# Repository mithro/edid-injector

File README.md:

A device for overriding / injecting EDID information into VGA/DVI/HDMI video
cables.

Based on the idea at
[vgaedidinjector](https://github.com/datenwolf/vgaedidinjector) but with a much
cheaper BOM. It shares no code or design elements with the original design
however.

Uses a Silicon Labs C8051F38x processor as;
 * Has two hardware I2C interfaces (input + output).
 * Has hardware USB subsystem.
 * Runs of 5V power with no external components.
 * Has internal oscillator.
 * I/O pins are 5V compatible.
 * Has good sdcc support.
 * Costs $1.83 USD in individual quantities.
 * Is hand solderable.

More info:
 * [Datasheet](http://www.silabs.com/Support%20Documents/TechnicalDocs/C8051F38x.pdf)
 * SiLab's part number: C8051F387-GQ
 * Digikey part Number: [336-2032-ND](http://www.digikey.com/product-detail/en/C8051F387-GQ/336-2032-ND/2601833)

# Other parts

## Connectors

 * HDMI connectors
  * **With** locking screw flange
   * `CONN RCPT HDMI W/FLANGE R/A SMD`
   * Manufacture part number: [FCI 10029449-002TLF]
   * Digikey part number: [609-1011-ND](http://www.digikey.com/product-search/en?KeyWords=609-1011-ND&WT.z_header=search_go)
   * [Datasheet](http://portal.fciconnect.com/Comergent//fci/drawing/10029449.pdf)
   * 
   * Cost: $1.17 USD in individual quantities.

  * **Without** locking screw flange.
   * `CONN HDMI RECPT 19POS SMT R/A`
   * Manufacture part number: [FCI 10029449-111RLF]
   * Digikey part number: [609-4614-1-ND](http://www.digikey.com/product-detail/en/10029449-111RLF/609-4614-1-ND/2785376)
   * [Datasheet](http://portal.fciconnect.com/Comergent//fci/drawing/10029449.pdf)
   * 
   * Cost: $0.73 USD in individual quantities.

# Editing

The designs in this repository was made using
[KiCad](http://www.kicad-pcb.org/) version **4.0.4**.

# License

Copyright 2014 Tim "mithro" Ansell licensed under a
Creative Commons Attribution-ShareAlike 4.0 International License.

You should have received a copy of the license along with this
work.  If not, see <http://creativecommons.org/licenses/by-sa/4.0/>.

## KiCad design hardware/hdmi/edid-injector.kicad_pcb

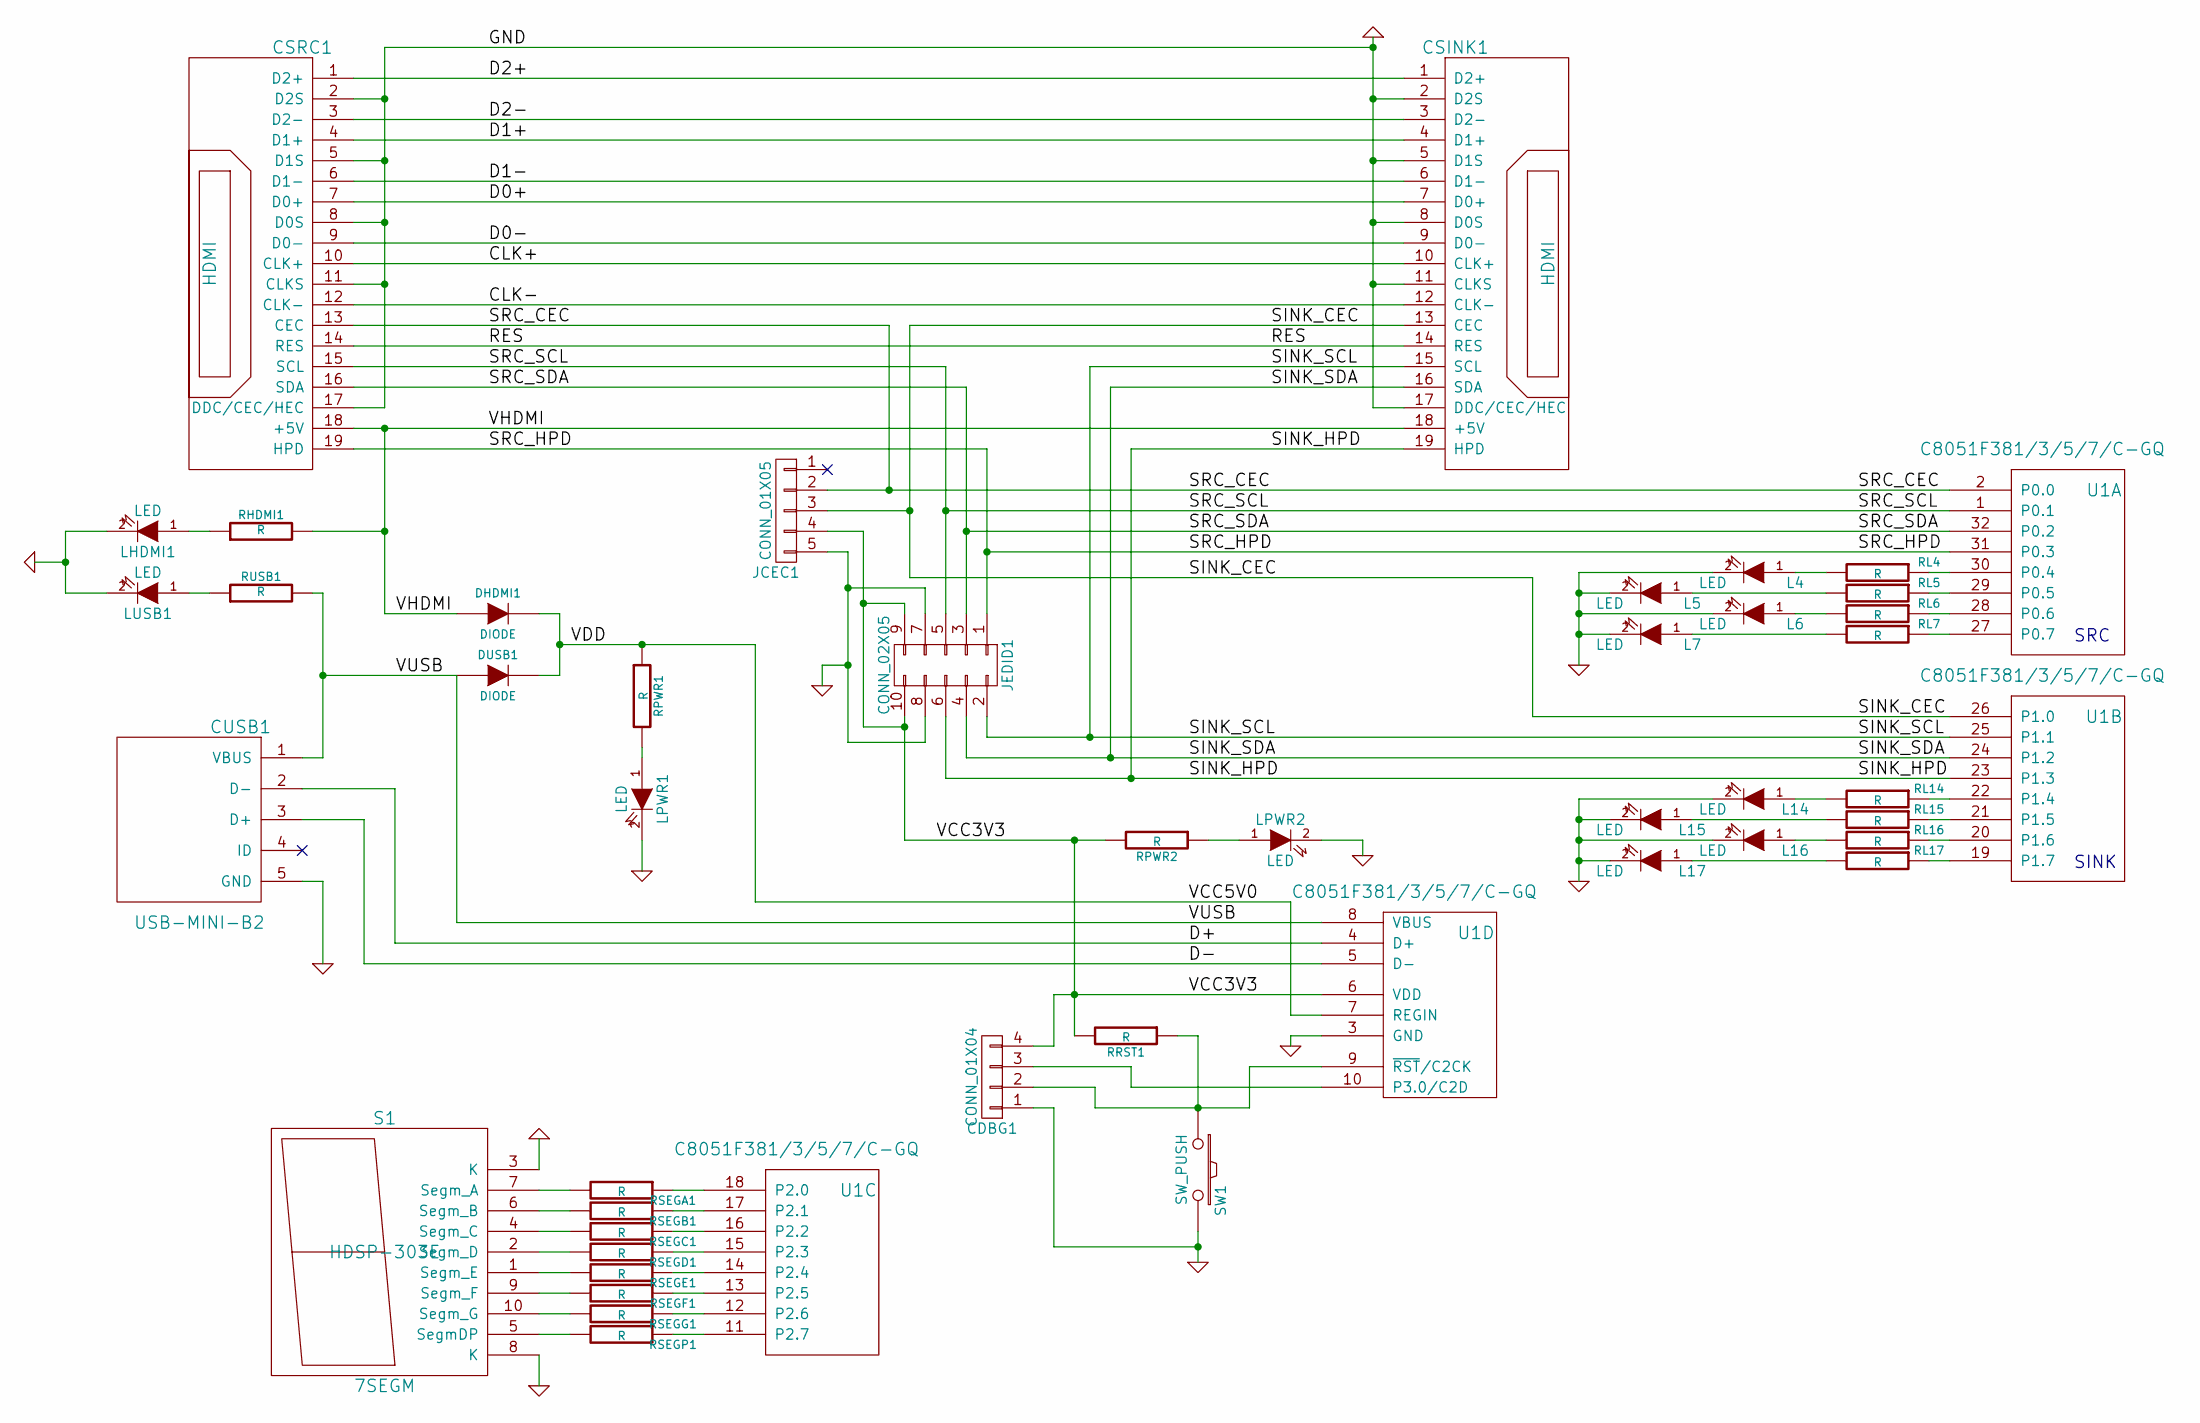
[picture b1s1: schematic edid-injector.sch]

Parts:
CDBG1: CONN_01X04; Pin_Header_Straight_1x04
CSINK1: HDMI; hdmi
CSRC1: HDMI; hdmi
CUSB1: USB-MINI-B2; micro-usb
DHDMI1: DIODE; sod323
DUSB1: DIODE; sod323
JCEC1: CONN_01X05; Pin_Header_Straight_1x05
JEDID1: CONN_02X05; Pin_Header_Straight_2x05
L4, L5, L6, L7, L14, L15, L16, L17: LED; LED_0805
LHDMI1: LED; LED_0805
LPWR1, LPWR2: LED; LED_0805
LUSB1: LED; LED_0805
RHDMI1: R; R_0402
RL4, RL5, RL6, RL7, RL14, RL15, RL16, RL17: R; R_0402
RPWR1, RPWR2: R; R_0402
RRST1: R; R_0402
RSEGA1: R; R_0402
RSEGB1: R; R_0402
RSEGC1: R; R_0402
RSEGD1: R; R_0402
RSEGE1: R; R_0402
RSEGF1: R; R_0402
RSEGG1: R; R_0402
RSEGP1: R; R_0402
RUSB1: R; R_0402
S1: 7SEGM; DIP-10__300
SW1: SW_PUSH; Pin_Header_Angled_1x02
U1: C8051F381/3/5/7/C-GQ; lqfp32

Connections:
/CLK+: CSINK1.10 (CLK+), CSRC1.10 (CLK+)
/CLK-: CSINK1.12 (CLK-), CSRC1.12 (CLK-)
/D0+: CSINK1.7 (D0+), CSRC1.7 (D0+)
/D0-: CSINK1.9 (D0-), CSRC1.9 (D0-)
/D1+: CSINK1.4 (D1+), CSRC1.4 (D1+)
/D1-: CSINK1.6 (D1-), CSRC1.6 (D1-)
/D2+: CSINK1.1 (D2+), CSRC1.1 (D2+)
/D2-: CSINK1.3 (D2-), CSRC1.3 (D2-)
/D+: CUSB1.2 (D-), U1.4 (D+)
/D-: CUSB1.3 (D+), U1.5 (D-)
/RES: CSINK1.14 (RES), CSRC1.14 (RES)
/SINK_CEC: CSINK1.13 (CEC), JCEC1.3, U1.26 (P1.0)
/SINK_HPD: CSINK1.19 (HPD), JEDID1.6, U1.23 (P1.3)
/SINK_SCL: CSINK1.15 (SCL), JEDID1.2, U1.25 (P1.1)
/SINK_SDA: CSINK1.16 (SDA), JEDID1.4, U1.24 (P1.2)
/SRC_CEC: CSRC1.13 (CEC), JCEC1.2, U1.2 (P0.0)
/SRC_HPD: CSRC1.19 (HPD), JEDID1.1, U1.31 (P0.3)
/SRC_SCL: CSRC1.15 (SCL), JEDID1.5, U1.1 (P0.1)
/SRC_SDA: CSRC1.16 (SDA), JEDID1.3, U1.32 (P0.2)
/VCC3V3: CDBG1.4, JCEC1.4, JEDID1.9, JEDID1.10, RPWR2.2, RRST1.2, U1.6 (VDD)
/VCC5V0: DHDMI1.2 (K), DUSB1.2 (K), RPWR1.1, U1.7 (REGIN)
/VHDMI: CSINK1.18 (+5V), CSRC1.18 (+5V), DHDMI1.1 (A), RHDMI1.2
/VUSB: CUSB1.1 (VBUS), DUSB1.1 (A), RUSB1.2, U1.8 (VBUS)
GND: CDBG1.1, CSINK1.2 (D2S), CSINK1.5 (D1S), CSINK1.8 (D0S), CSINK1.11 (CLKS), CSINK1.17 (DDC/CEC/HEC), CSRC1.2 (D2S), CSRC1.5 (D1S), CSRC1.8 (D0S), CSRC1.11 (CLKS), CSRC1.17 (DDC/CEC/HEC), CUSB1.5 (GND), JCEC1.5, JEDID1.7, JEDID1.8, L4.2 (K), L5.2 (K), L6.2 (K), L7.2 (K), L14.2 (K), L15.2 (K), L16.2 (K), L17.2 (K), LHDMI1.2 (K), LPWR1.2 (K), LPWR2.2 (K), LUSB1.2 (K), S1.3 (K), S1.8 (K), SW1.2, U1.3 (GND)
unnamed: CDBG1.2, RRST1.1, SW1.1, U1.9 (~RST~/C2CK)
unnamed: CDBG1.3, U1.10 (P3.0/C2D)
unnamed: L4.1 (A), RL4.2
unnamed: L5.1 (A), RL5.2
unnamed: L6.1 (A), RL6.2
unnamed: L7.1 (A), RL7.2
unnamed: L14.1 (A), RL14.2
unnamed: L15.1 (A), RL15.2
unnamed: L16.1 (A), RL16.2
unnamed: L17.1 (A), RL17.2
unnamed: LHDMI1.1 (A), RHDMI1.1
unnamed: LPWR1.1 (A), RPWR1.2
unnamed: LPWR2.1 (A), RPWR2.1
unnamed: LUSB1.1 (A), RUSB1.1
unnamed: RL4.1, U1.30 (P0.4)
unnamed: RL5.1, U1.29 (P0.5)
unnamed: RL6.1, U1.28 (P0.6)
unnamed: RL7.1, U1.27 (P0.7)
unnamed: RL14.1, U1.22 (P1.4)
unnamed: RL15.1, U1.21 (P1.5)
unnamed: RL16.1, U1.20 (P1.6)
unnamed: RL17.1, U1.19 (P1.7)
unnamed: RSEGA1.1, U1.18 (P2.0)
unnamed: RSEGA1.2, S1.7 (Segm_A)
unnamed: RSEGB1.1, U1.17 (P2.1)
unnamed: RSEGB1.2, S1.6 (Segm_B)
unnamed: RSEGC1.1, U1.16 (P2.2)
unnamed: RSEGC1.2, S1.4 (Segm_C)
unnamed: RSEGD1.1, U1.15 (P2.3)
unnamed: RSEGD1.2, S1.2 (Segm_D)
unnamed: RSEGE1.1, U1.14 (P2.4)
unnamed: RSEGE1.2, S1.1 (Segm_E)
unnamed: RSEGF1.1, U1.13 (P2.5)
unnamed: RSEGF1.2, S1.9 (Segm_F)
unnamed: RSEGG1.1, U1.12 (P2.6)
unnamed: RSEGG1.2, S1.10 (Segm_G)
unnamed: RSEGP1.1, U1.11 (P2.7)
unnamed: RSEGP1.2, S1.5 (SegmDP)

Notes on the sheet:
SRC
SINK

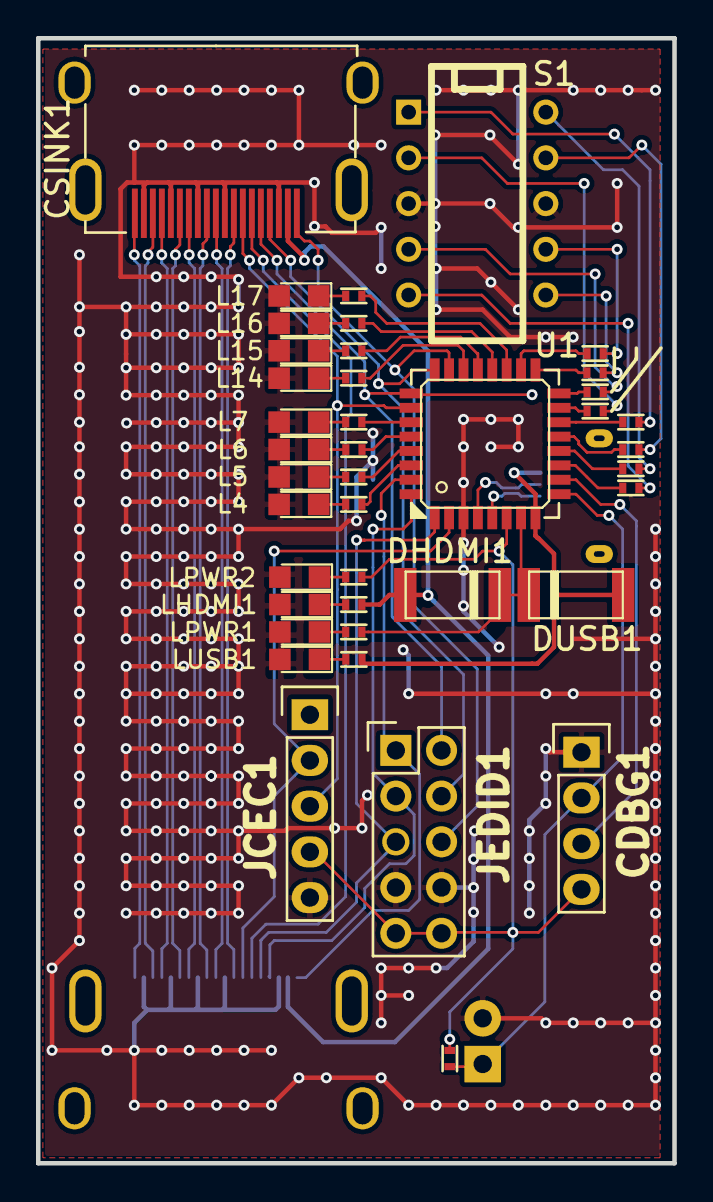
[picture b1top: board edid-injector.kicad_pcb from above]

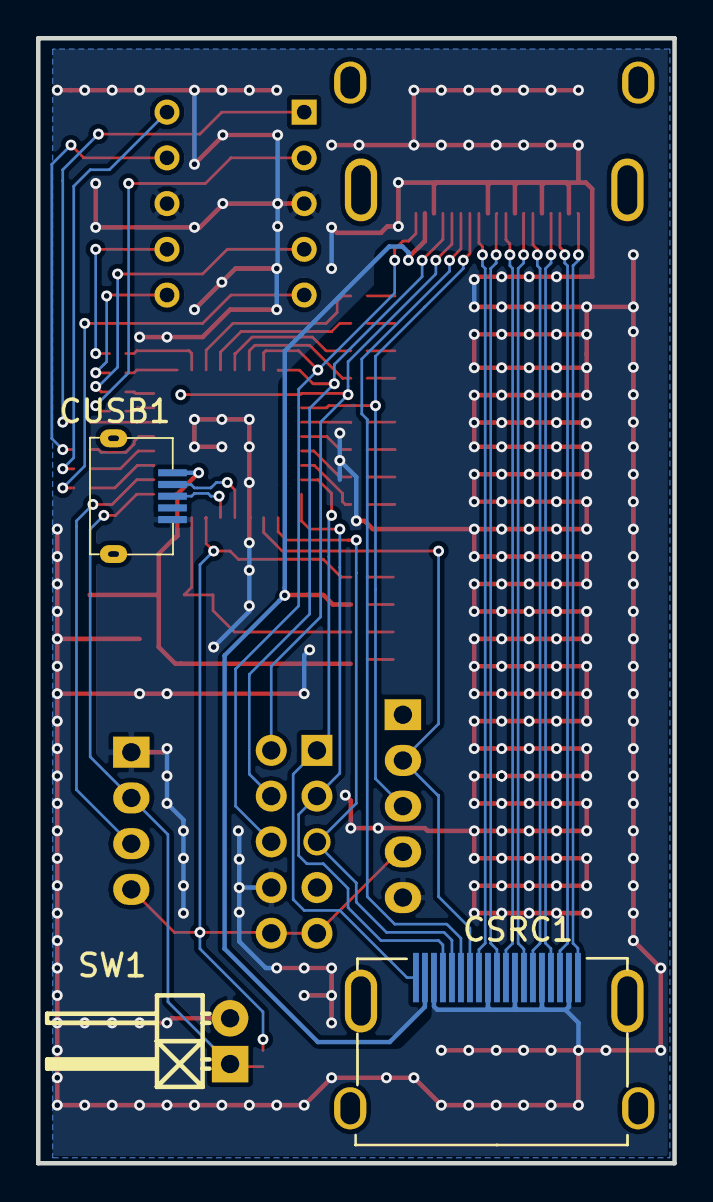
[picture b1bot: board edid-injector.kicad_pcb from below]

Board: 2 copper layers, 35.3 x 62.5 mm, 44 parts (3 on the bottom side), 62 nets.

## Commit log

2014-09-07 Initial commit with README and LICENSE file.
2014-09-08 Initial schematic.
2014-11-04 Temporary commit to allow John to take a look at the design.
2014-11-04 Fix schematic no-connects and some electrical rules
2014-11-04 Begin PCB layout - cleaning up rats nest
2014-11-15 Update 7-segment footprint and add Digikey Ref.
2014-11-15 Temp commit.
2014-11-15 Converging on sane placement for parts
2014-11-15 Closer to an autorouter-friendly layout.
2014-11-28 Better layout for PCB - autorouter is at -7 traces
2014-11-28 Preliminary route.
2014-11-30 Fixing the EDID jumper.
2014-11-30 Working on DRC info.
2014-11-30 Update PCB
2014-11-30 Connect everything up.
2016-08-03 Old changes.
2016-12-25 Moving things around slightly.
2016-12-25 Bunch of small tweaks.
2016-12-25 Fixing component assignments.
2016-12-25 Updating LICENSE to be CC-BY-SA and updating README a little.
2017-04-14 First PCB design from Phyllis.
2017-04-14 Trying to make things a little more uniform.
2017-04-14 Tweaking.
2017-04-14 Adding a TODO item.
